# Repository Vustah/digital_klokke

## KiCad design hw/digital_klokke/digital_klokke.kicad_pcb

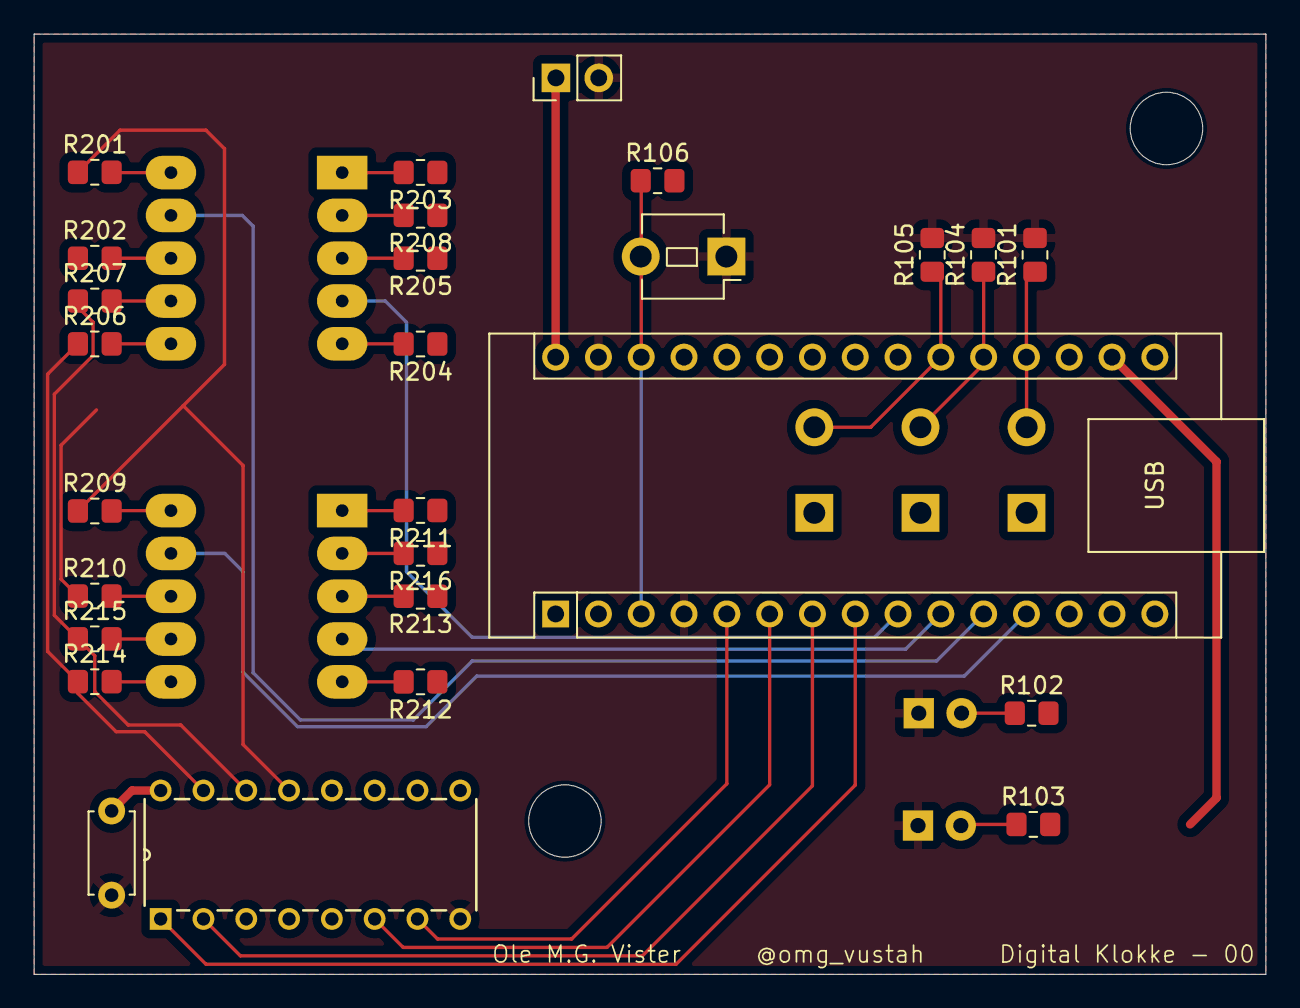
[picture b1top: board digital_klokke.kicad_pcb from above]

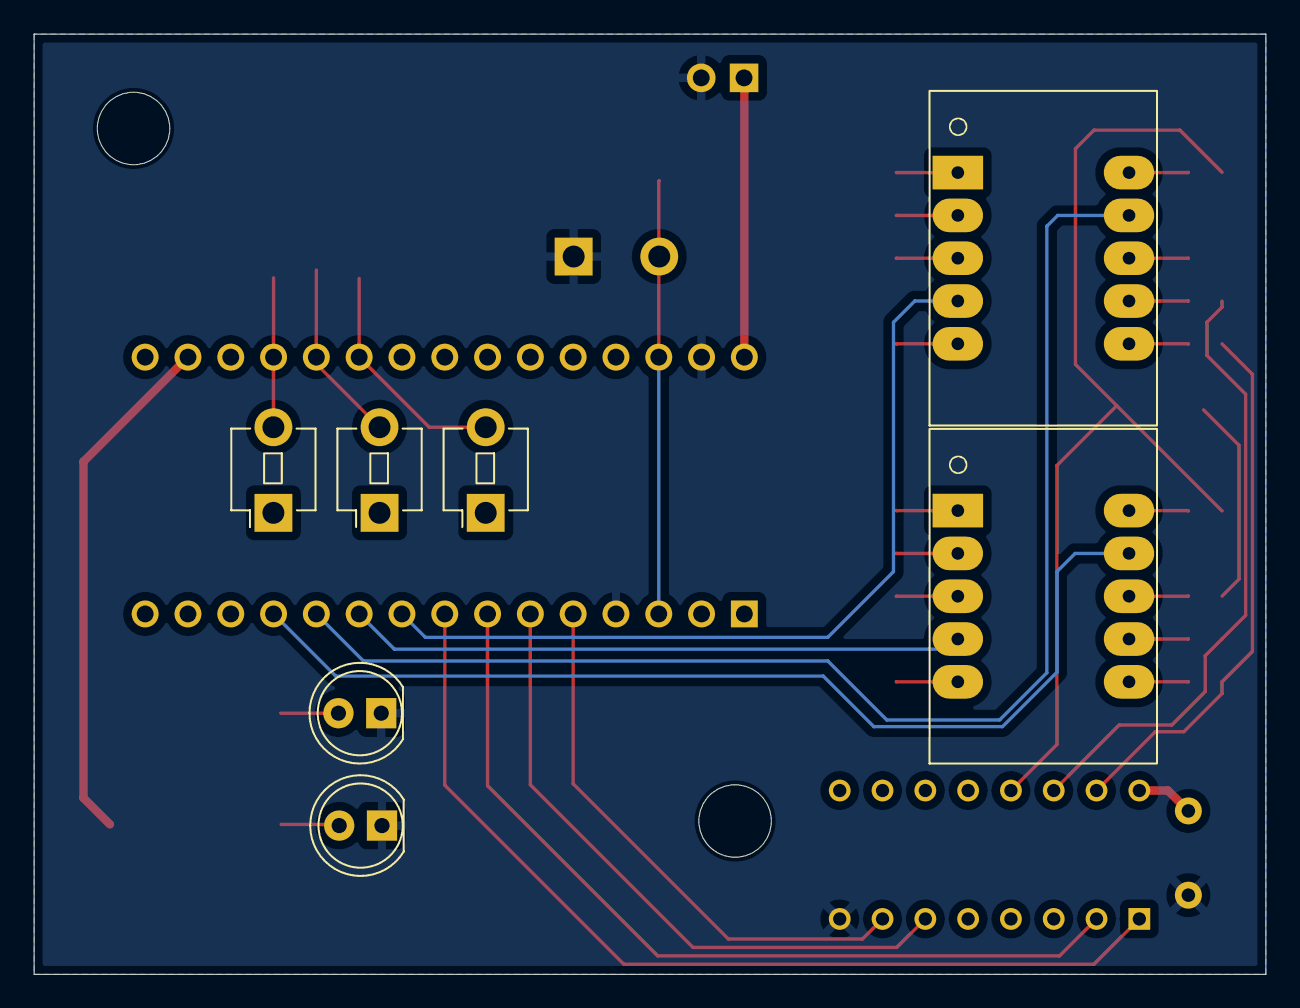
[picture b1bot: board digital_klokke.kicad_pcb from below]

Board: 4 copper layers, 73.1 x 55.8 mm, 36 parts (7 on the bottom side), 42 nets.

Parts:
A101: Arduino_Nano_Every; Arduino_Nano
C201: 100n; C_Disc_D4.7mm_W2.5mm_P5.00mm
D101, D102: green; LED_D5.0mm
D201, D202: LTD-4608JF; Lite-On LTD-4608JF
H101, H102: MountingHole; MountingHole_4.3mm_M4
J101: Conn_01x02_Pin; PinHeader_1x02_P2.54mm_Vertical
R101, R104, R105, R106: 1k; R_0805_2012Metric_Pad1.20x1.40mm_HandSolder
R102: 270; R_0805_2012Metric_Pad1.20x1.40mm_HandSolder
R103: 75; R_0805_2012Metric_Pad1.20x1.40mm_HandSolder
R201, R202, R203, R204, R205, R206, R207, R208, R209, R210, R211, R212, R213, R214, R215, R216: 470; R_0805_2012Metric_Pad1.20x1.40mm_HandSolder
SW101, SW102, SW103, SW104: SW_Push; SW_PUSH_1P1T_6x3.5mm_H5.0_APEM_MJTP1250
U201: 74LS47; N16

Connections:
+3V3: A101.17 (3V3), R103.2
+5V: A101.27 (+5V), C201.1, R102.2, R106.2, SW101.1, SW102.1, SW103.1, U201.3 (LT), U201.4 (BI), U201.5 (RBI), U201.16 (VCC)
+9V: A101.30 (VIN), J101.1
/A: A101.5 (D2), U201.7 (A)
/Adjust: A101.21 (A2), R105.1, SW103.2
/B: A101.8 (D5), U201.1 (B)
/C: A101.7 (D4), U201.2 (C)
/D: A101.6 (D3), U201.6 (D)
/Decrease_time: A101.20 (A1), R104.1, SW102.2
/Increase_time: A101.19 (A0), R101.1, SW101.2
/Minutes_ones: A101.12 (D9), D202.9 (Digit_1)
/Minutes_tens: A101.10 (D7), D202.4 (Digit_2)
/Seconds_ones: A101.11 (D8), D201.9 (Digit_1)
/Seconds_tens: A101.9 (D6), D201.4 (Digit_2)
/config_led: A101.13 (D10), R208.1, R216.1
/nRST: A101.3 (~RESET), A101.28 (~RESET), R106.1, SW104.2
GND: A101.4 (GND), A101.29 (GND), C201.2, D101.1 (K), D102.1 (K), J101.2, R101.2, R104.2, R105.2, SW104.1, U201.8 (GND)
unnamed: D101.2 (A), R102.1
unnamed: D102.2 (A), R103.1
unnamed: D201.10 (A), R201.2
unnamed: D201.8 (B), R202.2
unnamed: D201.1 (C), R203.2
unnamed: D201.5 (D), R204.2
unnamed: D201.2 (DP), R208.2
unnamed: D201.3 (E), R205.2
unnamed: D201.6 (F), R206.2
unnamed: D201.7 (G), R207.2
unnamed: D202.10 (A), R209.2
unnamed: D202.8 (B), R210.2
unnamed: D202.1 (C), R211.2
unnamed: D202.5 (D), R212.2
unnamed: D202.2 (DP), R216.2
unnamed: D202.3 (E), R213.2
unnamed: D202.6 (F), R214.2
unnamed: D202.7 (G), R215.2
unnamed: R201.1, R209.1, U201.13 (a)
unnamed: R202.1, R210.1, U201.12 (b)
unnamed: R203.1, R211.1, U201.11 (c)
unnamed: R204.1, R212.1, U201.10 (d)
unnamed: R205.1, R213.1, U201.9 (e)
unnamed: R206.1, R214.1, U201.15 (f)
unnamed: R207.1, R215.1, U201.14 (g)

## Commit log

2024-08-20 schematic main features done.
2024-08-21 added led for power indication. Started routing
2024-08-21 updated gitignore with lock-files
2024-08-26 added segment display footprint
2024-08-26 started working on sw
2024-08-31 started working
2024-08-31 addjusted timing function
2024-09-02 added correction function to code
2024-09-02 final design changes. Design freeze
2024-09-04 added resistor to each cathode
2024-09-04 added 'seconds counter'
2024-09-04 changed from 240 to 0 on pwm due to 1k res between cathode and io
2024-09-06 added 3D model for button
2024-09-08 copied pcb.step into mechanics folder.
2024-09-08 started working widh front housing part
2024-09-08 added leds to pcb model
2024-09-10 added amf-file
2024-09-10 changed digit pins to be in the right order
2024-09-10 whatever
2024-09-10 added .FCBak
2024-09-10 adjusted holes with bigger tolerances
2024-09-10 adjusted brightness of seconds dial
2024-09-12 new version of front cover.
2024-09-12 new version printed
2024-09-12 added backside
2024-09-12 added usb-C male
2024-09-12 added new display wait timer
2024-09-12 added function to increase and decrease visible time
2024-09-12 made function to adjust time better
2024-10-09 added adjusing of hours when setting the clock
2024-10-09 added 9V battery to repo
2024-10-09 finnished back-part
2024-10-09 Dev (#1)
    * initial commit
    * schematic main features done.
    * added led for power indication. Started routing
    * updated gitignore with lock-files
    * added segment display footprint
    * started working on sw
2024-10-09 Housing (#3)
    * initial commit
    * schematic main features done.
    * added led for power indication. Started routing
    * updated gitignore with lock-files
    * added segment display footprint
    * started working on sw
2024-10-10 changed hole depth
